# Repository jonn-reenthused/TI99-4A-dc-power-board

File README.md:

# TI99-4A-dc-power-board
moved to https://codeberg.org/Jonn-reenthused/TI99-4A-dc-power-board

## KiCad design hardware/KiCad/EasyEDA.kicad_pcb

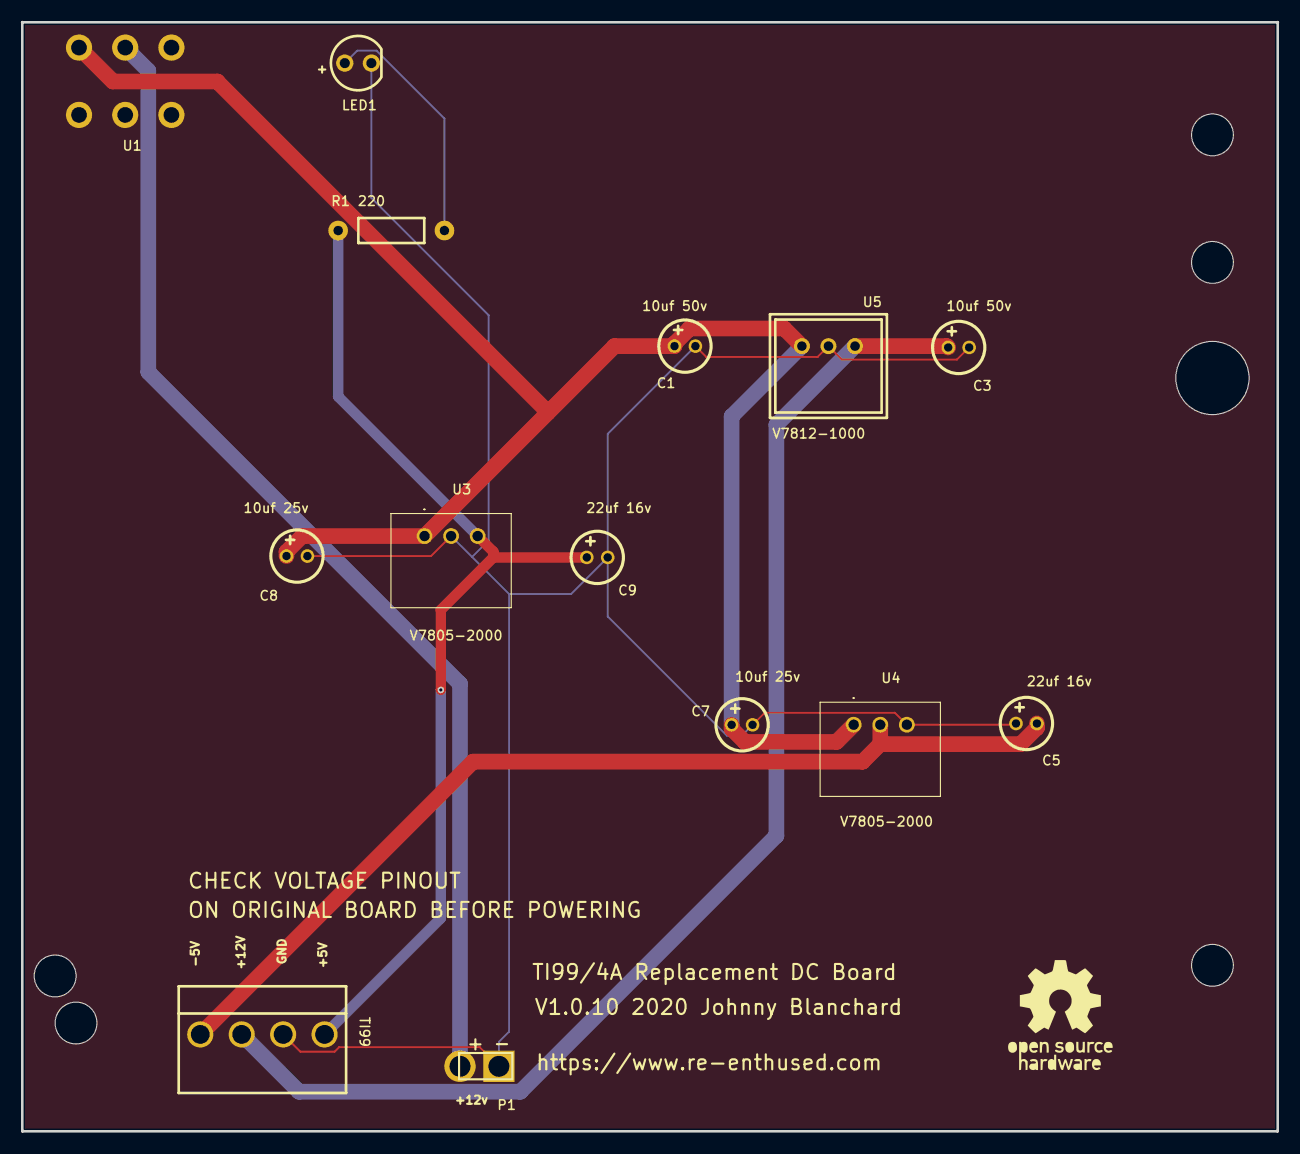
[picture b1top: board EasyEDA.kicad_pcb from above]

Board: 2 copper layers, 120.0 x 106.0 mm, 20 parts (0 on the bottom side), 7 nets.

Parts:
C1, C3: 10uf 50v; CAP-D5.0×F2.0
C5, C9: 22uf 16v; CAP-D5.0×F2.0
C7, C8: 10uf 25v; CAP-D5.0×F2.0
Hole_gge744: Hole_gge744
Hole_gge745: Hole_gge745
Hole_gge746: Hole_gge746
Hole_gge747: Hole_gge747
Hole_gge748: Hole_gge748
Hole_gge749: Hole_gge749
LED1: LED-5MM; LED-5MM/2.54
P1: Barrel Jack; HDR-1X2/2.54
R1: 220; L_AXIAL-0.4
TI99: Header-Male-2.54_1x4; DIP-1X4P-3.96MM-SK
U1: Slide_Switch; SLIDE_SWITCH
U3, U4: V7805-2000; V78031500
U5: V7812-1000; V7812W-500

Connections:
+5V: C9.1, R1.1, TI99.4, U3.3
+12V: C3.1, TI99.2, U5.3
-5V: C5.2, TI99.1, U4.2
DCIN: C1.1, C7.1, C8.1, U1.3, U3.1, U4.1, U5.1
GND: C1.2, C3.2, C5.1, C7.2, C8.2, C9.2, LED1.2, P1.2, TI99.3, U3.2, U4.3, U5.2
LED1_1: LED1.1, R1.2
U1_2: P1.1, U1.2

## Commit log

2023-10-09 Inital commit
2024-01-07 Added EasyEDA source files
2024-01-07 Added 3D power adaptor designed by Mr Lurch
2024-01-07 Added KiCad conversion - untested
2024-10-27 added funding link
